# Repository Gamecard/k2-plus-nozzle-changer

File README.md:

# K2 Plus Nozzle Changer – Düsenwechsler für den Creality K2 Plus

**English summary:** This repository contains a tool changer concept for the Creality K2 Plus 3D printer. Every colour gets its
own cartridge with its own hotend and its own filament path; the print head parks one cartridge in a passive dock at the front
and picks up another, so filament never has to be unloaded, cut or purged. Included are the mechanical design description
(prototype 19 v2), a complete, generator-built KiCad design of a new toolhead board (P19, revision 10) and a carrier
board for a Raspberry Pi Compute Module 5 as the printer's Klipper host (alpha 2), each with Gerber, BOM and
pick-and-place files. Status: designed and checked by calculation and simulation; not yet built or tested on a
printer. Not affiliated with Creality. Licences: hardware design CERN-OHL-W v2 (`LICENSE`), program code
GPL-3.0-or-later (`LICENSE-GPL-3.0.txt`).

Stand: konstruiert und rechnerisch geprüft, noch nicht gebaut und nicht am Drucker erprobt. Lizenz und Haftung:
[`LIZENZ-UND-HAFTUNG.md`](LIZENZ-UND-HAFTUNG.md).

## Worum es geht

Der Creality K2 Plus druckt mehrfarbig, indem er das Filament im Druckkopf wechselt: altes Filament zurückziehen, abschneiden,
neues laden und die Düse durchspülen. Das kostet Zeit und Material.

Dieses Projekt geht einen anderen Weg, ähnlich wie ein Werkzeugwechsler („Toolchanger“):

- Jede Farbe bekommt eine eigene **Patrone**. Eine Patrone ist ein gefrästes Aluminiumteil, in dem ein komplettes **Hotend**
  sitzt (Düse, Heizblock, Heatbreak – also der heiße Teil, der das Filament schmilzt) und durch das das Filament dieser Farbe läuft.
- Am Druckkopf sitzt immer genau eine Patrone. Die übrigen liegen in einer **Ablage** (Parkplätze) vorne über der Tür.
- Beim Farbwechsel legt der Kopf seine Patrone in der Ablage ab und nimmt eine andere auf. Das Filament bleibt dabei in seiner
  Patrone geladen – kein Entladen, kein Schneiden, kein Spülen.
- Der Antrieb des Filaments (Förderräder und Motor) bleibt fest im Kopf; die Förderräder greifen das Filament durch ein Fenster
  der jeweils angedockten Patrone.

Wichtigste Vorgabe der Konstruktion: Der Drucker soll **keine Druckfläche verlieren**. Die Düse liegt deshalb an derselben Stelle
wie beim Original-Kopf, der Kopf ist nicht breiter als das Original (55 mm), und die Ablage passt in den Spalt zwischen Kopf und
Tür.

## Wie ein Wechsel abläuft (Grundprinzip)

1. Der Kopf fährt vor den Platz der Ablage, auf dem er seine Patrone ablegen will.
2. Er fährt langsam nach vorn in den Platz. Die Patrone gleitet mit zwei Leisten auf ihrer Oberseite in Schienen der Ablage und
   rastet dort mit federnden Kugeln ein.
3. Zwei kleine **Hubmagnete** im Kopf öffnen kurz einen federbelasteten Riegel; die Patrone ist jetzt nur noch in der Ablage gehalten.
4. Der Kopf fährt zurück, fährt seitlich zur gewünschten anderen Patrone und mit offenem Riegel in deren Platz.
5. Die Hubmagnete werden stromlos, die Feder schließt den Riegel, ein **Hall-Sensor** meldet „Riegel zu“.
6. Der Kopf fährt zurück und zieht die Patrone dabei aus der Rastung. Die Patrone ist in jedem Moment entweder am Kopf verriegelt
   oder in der Ablage eingerastet.

Die nächste Patrone soll schon in der Ablage vorgeheizt werden. Gerechnet ergibt sich eine Wechselzeit von etwa 1,4 bis 1,6 Sekunden
(ohne Vorheizen und ohne die Fahrt vom Druckteil zur Ablage). Einzelheiten stehen in [`prototyp-19v2/README.md`](prototyp-19v2/README.md).

## Inhalt des Repositorys

| Ordner / Datei | Inhalt |
|---|---|
| [`prototyp-19v2/`](prototyp-19v2/) | Beschreibung der Mechanik (Prototyp 19 v2): Aufbau, Wechselablauf, Baugruppen, Kaufteile, offene Punkte; Bilder |
| [`prototyp-19v2/cad/`](prototyp-19v2/cad/) | CAD-Daten: SolidCraft-Modell, STEP der Baugruppe, STL der Druckteile (ohne fremde Bezugsmodelle, siehe dort) |
| [`cm5-carrier-pcb/`](cm5-carrier-pcb/) | Trägerplatine „K2-CM5-Träger Alpha 2“ für ein Raspberry Pi Compute Module 5 als Steuerrechner des Druckers: KiCad-Projekt, Python-Generator, Fertigungsdaten für JLCPCB, Lastenheft, Aufbau- und Bestellunterlagen |
| [`toolhead-pcb/`](toolhead-pcb/) | Eigene Kopfplatine „P19, Fassung 10“: KiCad-Projekt, Python-Generator, Fertigungsdaten für JLCPCB, Schaltungsbeschreibung, Kabelliste, Prüfberichte, Klipper-Beispielkonfiguration |
| [`LICENSE`](LICENSE) | Lizenztext CERN-OHL-W v2 (Hardware-Entwurf) |
| [`LICENSE-GPL-3.0.txt`](LICENSE-GPL-3.0.txt) | Lizenztext GNU GPL Version 3 (Programmcode) |
| [`LIZENZ-UND-HAFTUNG.md`](LIZENZ-UND-HAFTUNG.md) | Lizenzhinweis, Kurzfassung, Ausnahmen, Haftungsausschluss |

## Die Kopfplatine in einem Satz

Die Platine ersetzt die Original-Kopfplatine des K2 Plus. Sie wird mit 24–48 V versorgt, spricht mit dem Steuerrechner über
**CAN-Bus** (eine Zweidraht-Datenleitung, wie sie viele Klipper-Druckköpfe nutzen) und zusätzlich über **USB** (für Kamera und
Cartographer-Sensor über einen eingebauten USB-Hub) und trägt Motortreiber, Schaltausgänge und alle Sensoreingänge, die der
Wechsler braucht. Einzelheiten: [`toolhead-pcb/README.md`](toolhead-pcb/README.md).

**Wichtig:** Die Platine hat keinen Anschluss mehr für das Original-Kopfkabel des Druckers. Für den Betrieb ist ein **eigenes
Kabel vom Drucker zum Kopf** nötig (Versorgung + CAN und USB).

## Der Steuerrechner in einem Satz

Die Kopfplatine braucht einen Steuerrechner mit Klipper, der CAN und USB bereitstellt. Dafür liegt hier die Trägerplatine für
ein **Raspberry Pi Compute Module 5** bei: Sie ersetzt die Original-Steuerplatine des K2 Plus, wird mit 24 V versorgt, spricht
über RS485 und CAN mit dem Drucker und hat Anschlüsse für Display (DSI mit vier Datenleitungen, HDMI als Nachrüstoption,
USB für Touch), Lüfter und eine serielle Konsole. Die Vorgängerfassung Alpha 1 ist gebaut und läuft im Drucker; Alpha 2 ist
fertig entworfen und geprüft, aber noch nicht gefertigt. Einzelheiten: [`cm5-carrier-pcb/README.md`](cm5-carrier-pcb/README.md).

## Stand und bekannte offene Punkte (Stand 22.11.2026)

**Was geprüft ist** (nur rechnerisch bzw. in Simulation und im CAD):

- Mechanik: Platzbedarf gegen die Druckfläche, Kollisionsfreiheit des ganzen Wechselablaufs, Montierbarkeit jeder Schraube,
  Festigkeit und Steifigkeit (FEM), Eigenfrequenzen, Wärme an Kopf und Patrone, Toleranzen, Wechselzeit.
- Kopfplatine: elektrische Regelprüfung des Schaltplans (ERC) und der Platine (DRC) ohne Fehler, keine offenen Verbindungen,
  Netzliste gegen eine unabhängige Soll-Tabelle geprüft, kritische Leitungen (Längen, Breiten, USB-Paare) geprüft, Fertigungsnutzen
  geprüft. Steckbarkeit aller Stecker und Kabelwege im CAD-Modell des Kopfs geprüft.

**Was nicht geprüft ist:**

- Nichts ist gebaut. Keine Patrone, keine Ablage, keine Platine wurde gefertigt oder in Betrieb genommen.
- Viele Kaufteil-Maße und -Kennwerte sind Annahmen oder aus Datenblättern übernommen, nicht am Teil gemessen.
- Die Firmware-Seite (Klipper-Konfiguration, Makros für den Wechsel) liegt nur als Entwurf vor und ist nirgends eingespielt.

**Offene Punkte (Auswahl):**

- Andockkraft: Der Kopf drückt beim Andocken mit etwa 50–64 N gegen die Ablage. Ob der Y-Antrieb des Druckers das sicher
  schafft, ist nur abgeschätzt und muss am Drucker bestätigt werden.
- Zum Andocken fährt der Kopf 18,5 mm weiter nach vorn als beim Drucken. Ob die Fahrgrenze in der Klipper-Konfiguration dafür
  reicht oder angepasst werden muss, ist offen.
- Führung der Patronenkabel und Filamentschläuche vom Kopf zur Filamentzufuhr (CFS) ist noch nicht ausgelegt.
- Heizungen und Temperaturfühler der Patronen hängen an einer eigenen **Heizplatine**, die noch nicht Teil dieses Repositorys ist
  (Konzeptstand).
- Kopfplatine: Lagerbestand des 2-poligen JST-GH-Steckers beim Bestücker am Bestelltag prüfen; Pin 1 und Drehung der gepolten
  Teile in der Bestellvorschau ansehen; das neue Kabel Drucker → Kopf ist zu konfektionieren.
- Einige Kabelabgänge an Geräten (Bauteillüfter, LED-Kette, Probe) sind angenommen, nicht gemessen.

## Lizenz und Haftung

Der Hardware-Entwurf steht unter der **CERN Open Hardware Licence Version 2 – Weakly Reciprocal (CERN-OHL-W v2)**, der
Programmcode (Generator, Werkzeuge, Bauskript, Klipper-Beispiel) unter der **GNU General Public License Version 3 oder
später**. Die vollständigen Lizenztexte enthalten [`LICENSE`](LICENSE) und [`LICENSE-GPL-3.0.txt`](LICENSE-GPL-3.0.txt); Kurzfassung, Ausnahmen (KiCad-Bibliotheken, Herstellerdaten, fremde Modelle) und den
Haftungsausschluss enthält [`LIZENZ-UND-HAFTUNG.md`](LIZENZ-UND-HAFTUNG.md). Hinweis: Die Platinen arbeiten mit
bis zu 48 V, Motor- und Heizlasten.

## Hinweis zu Marken

Dieses Projekt ist **kein Produkt von Creality** und steht in keiner Verbindung zu Creality oder anderen genannten Herstellern.
Marken- und Produktnamen (z. B. Creality, K2 Plus, CFS, Bambu Lab, Micro Swiss, Cartographer, JST, JLCPCB) dienen nur der
Bezeichnung der Teile und Geräte, mit denen der Entwurf zusammenarbeiten soll.

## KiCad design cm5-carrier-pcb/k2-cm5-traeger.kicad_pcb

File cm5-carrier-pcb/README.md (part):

# K2-CM5-Träger Alpha 2 – Layout-Entwurf (22.11.2026)

**English summary:** Carrier board for a Raspberry Pi Compute Module 5 that replaces the original controller board of the
Creality K2 Plus (Klipper host): 24 V input, RS485 and CAN to the printer, the printer's original 50-pin flat cable, DSI
display connector with 4 lanes, optional HDMI (connector not populated), USB-A for touch, switched 5 V for displays, fan and
debug console connectors. The KiCad files are produced by a Python generator. Status: design complete and checked
(ERC/DRC clean), not yet manufactured or tested. Predecessor Alpha 1 was built and runs in the printer.

Stand: Entwurf fertig und geprüft, noch nicht gefertigt und nicht erprobt. Lizenz: Hardware-Unterlagen **CERN-OHL-W v2**,
Programmcode (Generator, Werkzeuge) **GPL-3.0-or-later**; Lizenz und Haftung: [`../LIZENZ-UND-HAFTUNG.md`](../LIZENZ-UND-HAFTUNG.md).
Quelle: `github.com/Gamecard/k2-plus-nozzle-changer`.

> **Status (22.11.2026): Alpha 2 – Entwurf, nicht bestellt, nicht gefertigt.** Grundlage ist Alpha 1 (gefertigt, seit
> 09.11.2026 im Drucker). Unverändert: Breite, Lochbild, CM5-Lage, Flachkabel J1, 24-V-Eingang J7, CAN J9b, RS485 J11,
> Notfall-USB J10. Neu bzw. geändert: Display-Stecker J12 (richtig belegt, 4 Lanes), freie Displaywahl mit HDMI
> (Buchse J16 als Nachrüstoption, nicht bestückt), USB-A J17 für Touch über einen Hub, Display-5 V J13 bis 2,6 A,
> Lüfter J14, Konsole J15, CAN-Abschluss als Lötbrücke, Kante B um 16,5 mm verlängert, eigener Nutzen für die
> Fertigung. Begründungen: [`ALPHA2-LASTENHEFT.md`](ALPHA2-LASTENHEFT.md). Prüfstand: [Prüfungen](#prüfungen).

> **Unterlagen:** [`ALPHA2-LASTENHEFT.md`](ALPHA2-LASTENHEFT.md) · [`BESTELLUNG-JLC.md`](BESTELLUNG-JLC.md) ·
> [`KOMPROMISSE-UND-OFFENE-PUNKTE.md`](KOMPROMISSE-UND-OFFENE-PUNKTE.md) · Inbetriebnahme (Alpha 1, mit Abweichungen):
> [`AUFBAU-UND-INBETRIEBNAHME.md`](AUFBAU-UND-INBETRIEBNAHME.md) · Konzept: [`KONZEPT.md`](KONZEPT.md) ·
> Bestückungsübersicht: `ausgabe/bestueckung_oben.png`, `ausgabe/bestueckung_unten.png`

## Zweck

Der Träger ersetzt das T113-Upper-Board des K2 Plus. Er trägt ein **Raspberry Pi Compute Module 5 (CM5)** direkt (zwei
100-pol. Steckverbinder, 1,5 mm Bauhöhe), versorgt es aus den 24 V des Druckers und verbindet es über das
Original-Flachkabel (J1) mit dem Drucker. Er sitzt hinter dem Display im Displaygehäuse (Dome L1–L4), Bauteilseite
zum Display.

## Unterschiede zu Alpha 1

| Punkt | Alpha 1 | Alpha 2 | Stecker / CM5-Pins |
|---|---|---|---|
| Umriss | 90,0 × 56,1 mm | **90,0 × 72,6 mm** (Kante B 16,5 mm länger, alle Alpha-1-Lagen gleich) | – |
| Display-Stecker | Hirose FH12 (Kontakte unten), Belegung **gespiegelt** | Buchse mit **Kontakten oben**, Pad n = Kabelleiter n, jeder Kontakt gegen das CM5-IO-Board geprüft; Kabel **mit Kontakten nach oben** stecken | J12 |
| DSI-Lanes | D0, D1 + Takt | **D0–D3 + Takt**, 100 Ω, ohne Via, gleich lang | J12; CM5 175–189, **193/195 (D2), 194/196 (D3)** |
| HDMI | – | **J16** HDMI Typ A, alle 4 TMDS-Paare 100 Ω ohne Via, DDC/CEC/HPD mit ESD, 5 V begrenzt – **Buchse nicht bestückt** | HDMI1: 143–166 |
| USB-Host (Touch) | – | **J17** USB-A über Hub U19 (CH334R) am Hub-Port, 5 V 0,89–1,06 A, schaltbar | USB3-1 (163/165), VBUS_EN (Pin 111) |
| 5 V für Displays | – | **J13** JST GH 6-pol., Lastschalter **2,33–2,63 A**, an nach Reset, abschaltbar | GPIO26 (Pin 24) EN, GPIO6 (Pin 30) Fehler |
| Lüfter | – | **J14** JST SH 4-pol. wie Raspberry Pi 5, 5 V geschaltet (0,49–0,60 A) | Pin 16 Fan_Tacho, Pin 19 Fan_PWM, Pin 111 VBUS_EN |
| Konsole | – | **J15** JST SH 3-pol. nach Pi-Debugstecker-Spezifikation | GPIO8/9 (Pin 39/40) = UART3 |
| CAN-Controller | SPI0 (GPIO8–11) | **SPI1** (GPIO18–21), INT GPIO25 unverändert | Pins 49/26/27/25 statt 39/40/44/38 |
| CAN-Abschluss | Stiftleiste + Kappe (Kappe fehlte ab Werk) | **Lötbrücke, ab Werk geschlossen** | JP_CAN_TERM |
| RS485-Abschluss | Stiftleiste | **Lötbrücke, ab Werk offen** | JP_485_TERM |
| Fertigung | Einzelplatine, JLC setzte Ränder mit V-Cut | **eigener Nutzen** mit Frässchlitz und Mausbiss-Stegen | – |
| Bauergebnis | jede Generierung anders | zweimal gebaut = byte-gleich | – |

Weggelassen wurde **keine** Funktion von Alpha 1. Die Hub-Leitung am Flachkabel J1 läuft jetzt über den Hub U19
(Port 1); das Gerät am Flachkabel sieht weiterhin einen USB-2.0-Anschluss.

## Welche Displays gehen

| Display | Anschluss | Versorgung | Grenzen |
|---|---|---|---|
| DSI 22-pol. (Raspberry Pi 5 / CM5-IO-Belegung, 1–4 Lanes), z. B. Raspberry Pi Touch Display 2, Waveshare DSI | J12, Kabel mit Kontakten nach oben | 3,3 V aus J12 (eigener Wandler, 2 A); 5 V bei Bedarf aus J13 | nur DSI1 (ein Display); Touch über I2C an J12 |
| DSI 15-pol. (Raspberry-Pi-4-Belegung, 2 Lanes) | J12 über Adapterkabel 22 → 15 (Raspberry-Pi-5-Displaykabel) | wie oben | nur 2 Lanes (D2/D3 sind am 15-pol. Kabel nicht vorhanden) |
| HDMI mit USB-Touch | J16 (Buchse **nachlöten**, Anleitung unten) + J17 USB-A | 5 V aus J13 (bis 2,33 A sicher, siehe Budget) oder über das USB-Kabel aus J17 (≤ 0,89 A) | HDMI1 bis 4K60 laut CM5-Datenblatt; ohne nachgelötete Buchse kein HDMI |
| HDMI ohne Touch | J16 (nachlöten) | J13 | wie oben |
| Displays mit eigenem 5-V-Eingang (Stiftleiste, Micro-USB, USB-C) | J12 oder J16 | **J13**, Kabel GH 6-pol. → Displaystecker | ≥ 2 A nur, wenn CM5 + USB-A + Lüfter zusammen unter ≈ 3 A bleiben (normal ≈ 1,4 A) |

## Stecker

Draufsicht von oben, Kante A links (Flachkabel), B oben (HDMI/USB-A), C rechts (Display), D unten.

| Stecker | Funktion | Bauform | Belegung | Lage |
|---|---|---|---|---|
| J1 | Original-Flachkabel zum Drucker | FPC 50-pol. 0,5 mm (XUNPU FPC-05FB-50PH20) | wie Alpha 1 (Pin n = Breakout n) | Kante A |
| J7 | 24-V-Eingang | XT30 liegend | 2 = +24 V, 1 = GND | Kante A oben |
| J9b | CAN (Toolhead/Mainboard-Ersatz) | JST GH 3-pol. stehend | 1 CANH, 2 CANL, 3 GND | innen, rechts von L1 (Drossel) |
| J10 | Notfall-USB-C (rpiboot, 5-V-Notversorgung) | USB-C stehend | USB 2.0 OTG | innen, links |
| J11 | RS485-Abgriff | JST GH 3-pol. stehend | 1 A, 2 B, 3 GND | Kante D |
| **J12** | **DSI-Display** (MIPI1 = DSI1) | FPC 22-pol. 0,5 mm, **Kontakte oben**, Schieber | Raspberry Pi 5 / CM5-IO (Tabelle unten) | Kante C, Mitte |
| **J13** | **5 V für Displays** | JST GH 6-pol. stehend | 1–3 = 5 V, 4–6 = GND | Kante B rechts |
| **J14** | **Lüfter** | JST SH 4-pol. stehend | 1 = 5 V, 2 = PWM, 3 = GND, 4 = Tacho (wie Pi 5) | rechts oben neben dem CM5 |
| **J15** | **Serielle Konsole** | JST SH 3-pol. stehend | 1 = RX (in den CM5), 2 = GND, 3 = TX (aus dem CM5) | Kante C unten, unter J12 |
| **J16** | **HDMI** (HDMI1) – **nicht bestückt** | HDMI Typ A liegend (Amphenol 10029449-001RLF) | HDMI-Norm | Kante B Mitte |
| **J17** | **USB-A Host** (Touch, USB 2.0) | USB-A liegend (Molex 67643-2911) | USB-Norm | Kante B links |

## Lötbrücken und Steckbrücke

*Lötbrücke:* zwei oder drei Kupferflächen nebeneinander. „Geschlossen“ heißt: ab Werk durch einen schmalen Kupfersteg
verbunden – zum Ausschalten den Steg mit einem Cutter durchtrennen, zum Wiedereinschalten Lötzinn darüber. „Offen“
heißt: ab Werk getrennt – zum Einschalten mit einem Zinntropfen verbinden.

| Bezeichnung | Seite | Funktion | ab Werk |
|---|---|---|---|
| JP_CAN_TERM | oben | CAN-Abschluss 120 Ω (Träger = Busende) | **geschlossen** |
| JP_485_TERM | oben | RS485-Abschluss 120 Ω | **offen** (Bus wird heute vom K2-Mainboard abgeschlossen) |
| JP2 / JP3 | unten | RS485-Ruhevorspannung A/B | geschlossen |
| JP5 | unten | 5-V-Notversorgung über USB-C in den Power-Mux | geschlossen |
| JP6 / JP7 | unten | CC1/CC2 der USB-C-Buchse an den CM5 (R43/R44 nur, wenn offen) | geschlossen |
| JP_FAN_EN (3-pol.) | unten | Freigabe Lüfter-5 V: 1–2 = VBUS_EN (aus, wenn der CM5 heruntergefahren ist), 2–3 = CM5-3,3 V | **1–2 geschlossen** |
| JP_BOOT | oben | Stiftleiste: Steckbrücke gesteckt = rpiboot über J10 | offen (keine Kappe) |

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
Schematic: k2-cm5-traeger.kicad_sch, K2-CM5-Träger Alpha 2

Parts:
C1, C2: 22p; C_0805_2012Metric; MPN CL21C220JBANNNC; LCSC C1804
C3, C5, C6, C7, C11, C12, C22, C25, C27, C30, C31, C32, C33, C39, C40, C42, C43, C46, C47: 100n; C_0805_2012Metric; MPN CC0805KRX7R9BB104; LCSC C49678
C4, C18, C34, C37, C41, C44, C45: 10u; C_0805_2012Metric; MPN CL21A106KAYNNNE; LCSC C15850
C8: 22n; C_0805_2012Metric; MPN CC0805KRX7R9BB223; LCSC C107147
C9, C10: 10u50; C_1206_3216Metric; MPN CL31A106KBHNNNE; LCSC C13585
C13: 33p; C_0805_2012Metric; MPN CC0805JRNPO9BN330; LCSC C107115
C14, C15, C16, C17, C19, C20, C21: 22u25; C_1206_3216Metric; MPN CL31A226KAHNNNE; LCSC C12891
C28: 1n2kV; C_1206_3216Metric; MPN 1206B102K202NT; LCSC C9196
C35, C36, C38, C48, C49: 22u6; C_0805_2012Metric; MPN CL21A226MQQNNNE; LCSC C5674
D1, D2, D3, D20: USBLC6-2SC6; SOT-23-6; MPN USBLC6-2SC6; LCSC C7519
D4, D19: SRV05-4; SOT-23-6; MPN SRV05-4; LCSC C5240367
D5: SM712; SOT-23; MPN SM712; LCSC C502564
D6: NUP2105L; SOT-23; MPN NUP2105LT1G; LCSC C14486
D7: TPD4E05U06; USON-10_2.5x1.0mm_P0.5mm; MPN TPD4E05U06DQAR; LCSC C138714
D8: SMFJ28A; D_SOD-123F; MPN SMFJ28A; LCSC C5439963
D10: LED 0805 rot; LED_0805_2012Metric; MPN NCD0805R1; LCSC C84256
D11, D12, D13: LED 0805 grün; LED_0805_2012Metric; MPN KT-0805G; LCSC C2297
D14: LED 0805 gelb; LED_0805_2012Metric; MPN KT-0805Y; LCSC C2296
D15, D16: SMF5.0A; D_SOD-123F; MPN SMF5.0A; LCSC C193402
F1: 3A tauschbar; Sicherungshalter_Littelfuse_157_Nano2_2410; MPN 0157003.DR; LCSC C187520
F3: PTC 0,5A 30V; Fuse_1812_4532Metric; MPN SMD1812P050TF/30; LCSC C12559
FID1, FID2, FID3, FID4, FID5, FID6: Passermarke; Fiducial_1mm_Mask2mm
H1, H2, H3, H4: Befestigung T113-Platz (M3); Bohrung_3.5mm_T113_Kopf5.5mm
J1: FPC-05FB-50PH20; FFC_XUNPU_FPC-05FB-50PH20_1x50_P0.5mm_Horizontal; MPN FPC-05FB-50PH20; LCSC C2856838
J2: CM5 (2x DF40C-100DS-0.4V(51)); CM5_Modul_2xDF40C-100DS-0.4V51_1.5mm; MPN DF40C-100DS-0.4V(51); LCSC C597931
J7: XT30 24V; AMASS_XT30PW-M_1x02_P2.50mm_Horizontal; MPN XT30PW-M30.G.Y; LCSC C431092
J9b: CAN H/L/GND; JST_GH_BM03B-GHS-TBT_1x03-1MP_P1.25mm_Vertical; MPN BM03B-GHS-TBT(LF)(SN); LCSC C161691
J10: USB-C stehend; USB_C_Buchse_stehend_16P_TYPE-C-16P-LTH6.8; MPN TYPE-C 16P LTH6.8; LCSC C5187468
J11: RS485 A/B/GND; JST_GH_BM03B-GHS-TBT_1x03-1MP_P1.25mm_Vertical; MPN BM03B-GHS-TBT(LF)(SN); LCSC C161691
J12: DSI 22-pol. Kontakte oben; FPC_0.5K-AS-22PWB_1x22_P0.5mm_Kontakte_oben_Horizontal; MPN 0.5K-AS-22PWB-RW; LCSC C53120858
J13: 5V Display; JST_GH_BM06B-GHS-TBT_1x06-1MP_P1.25mm_Vertical; MPN BM06B-GHS-TBT(LF)(SN); LCSC C189892
J14: Lüfter; JST_SH_BM04B-SRSS-TB_1x04-1MP_P1.00mm_Vertical; MPN BM04B-SRSS-TBT(LF)(SN); LCSC C495539
J15: Konsole UART; JST_SH_BM03B-SRSS-TB_1x03-1MP_P1.00mm_Vertical; MPN BM03B-SRSS-TBT(LF)(SN); LCSC C495538
J16: HDMI A (n. b.); HDMI_A_Amphenol_10029449-x01xLF_Horizontal; MPN 10029449-001RLF; LCSC C428493; not fitted
J17: USB-A Host; USB_A_Molex_67643_Horizontal; MPN 67643-2911; LCSC C293351
JP2: Bias A; SolderJumper-2_P1.3mm_Bridged_RoundedPad1.0x1.5mm
JP3: Bias B; SolderJumper-2_P1.3mm_Bridged_RoundedPad1.0x1.5mm
JP5: VBUS; SolderJumper-2_P1.3mm_Bridged_RoundedPad1.0x1.5mm
JP6: CC1; SolderJumper-2_P1.3mm_Bridged_RoundedPad1.0x1.5mm
JP7: CC2; SolderJumper-2_P1.3mm_Bridged_RoundedPad1.0x1.5mm
JP_485_TERM: 485 120R; SolderJumper-2_P1.3mm_Open_RoundedPad1.0x1.5mm
JP_BOOT: RPIBOOT; Stiftleiste_1x2_P2.54mm_SMD_stehend; MPN HX PZ2.54-1x2P TP-YQ; LCSC C41417359
JP_CAN_TERM: CAN 120R; SolderJumper-2_P1.3mm_Bridged_RoundedPad1.0x1.5mm
JP_FAN_EN: 1-2 zu; SolderJumper-3_P1.3mm_Bridged12_RoundedPad1.0x1.5mm
L1: 4,7µH; L_Changjiang_FXL0630; MPN FXL0630-4R7-M; LCSC C167220
L2: 2,2µH; L_1008_2520Metric; MPN WPN252010H2R2MT; LCSC C97031
R1, R2, R3, R4, R15, R16, R20, R28, R41, R42: 1k; R_0805_2012Metric; MPN 0805W8F1001T5E; LCSC C17513
R9, R10, R45, R54, R58: 100k; R_0805_2012Metric; MPN 0805W8F1003T5E; LCSC C149504
R11, R12, R13, R14, R18, R30, R50, R52, R53, R55: 10k; R_0805_2012Metric; MPN 0805W8F1002T5E; LCSC C17414
R17, R19, R56, R57: 120; R_0805_2012Metric; MPN 0805W8F1200T5E; LCSC C17437
R23: 5m; R_2512_6332Metric; MPN RLM25FEER005; LCSC C185817
R24: 10m; R_2512_6332Metric; MPN HoLLR2512-2W-10mR-1%; LCSC C2962784
R26: 105k; R_0805_2012Metric; MPN 0805W8F1053T5E; LCSC C17410
R27: 19k1; R_0805_2012Metric; MPN 0805W8F1912T5E; LCSC C17508
R29: 33k; R_0805_2012Metric; MPN 0805W8F3302T5E; LCSC C17633
R31: 18k7; R_0805_2012Metric; MPN 0805W8F1872T5E; LCSC C17499
R36, R37: 75; R_0805_2012Metric; MPN 0805W8F750JT5E; LCSC C17820
R38, R48, R49: 2k2; R_0805_2012Metric; MPN 0805W8F2201T5E; LCSC C17520
R39, R40: 470; R_0805_2012Metric; MPN 0805W8F4700T5E; LCSC C17710
R43, R44: 5k1; R_0805_2012Metric; MPN 0805W8F5101T5E; LCSC C27834; not fitted
R46, R51: 22k; R_0805_2012Metric; MPN 0805W8F2202T5E; LCSC C17560
R59: 150k; R_0805_2012Metric; MPN 0805W8F1503T5E; LCSC C17470
R60: 56k; R_0805_2012Metric; MPN 0805W8F5602T5E; LCSC C17756
T1: H1102NLT; Uebertrager_SMD_H1102NLT_12.7x7.1mm; MPN H1102NLT; LCSC C18584
TP1, TP2: GND; TestPoint_Pad_D1.5mm
TP3: 5V; TestPoint_Pad_D1.5mm
TP4: 3V3; TestPoint_Pad_D1.5mm
TP5: RUN; TestPoint_Pad_D1.5mm
TP6: BOOT; TestPoint_Pad_D1.5mm
TP7: PWR; TestPoint_Pad_D1.5mm
TP10: 24V; TestPoint_Pad_D1.5mm
TP11: BR5V; TestPoint_Pad_D1.5mm
TP12: PWR_FAIL; TestPoint_Pad_D1.5mm
U1: MCP2518FD; SOIC-14_3.9x8.7mm_P1.27mm; MPN MCP2518FDT-H/SL; LCSC C626759
U2: SN65HVD230; SOIC-8_3.9x4.9mm_P1.27mm; MPN SN65HVD230DR; LCSC C12084
U3: THVD1450DR; SOIC-8_3.9x4.9mm_P1.27mm; MPN THVD1450DR; LCSC C2671361
U4, U5: INA226; MSOP-10_3x3mm_P0.5mm; MPN INA226AIDGSR; LCSC C49851
U7: LMR51450SDRRR; WSON-12-1EP_3x3mm_P0.5mm_EP1.5x2.5mm; MPN LMR51450SDRRR; LCSC C6890985
U8: TPS2121RUXR; Texas_RUX_VQFN-HR-12_2x2.5mm_P0.5mm; MPN TPS2121RUXR; LCSC C485916
U10, U11, U12, U13, U17: SN74LVC1G125; SOT-23-5; MPN SN74LVC1G125DBVR; LCSC C23654
U14: TLV62569DBVR; SOT-23-5; MPN TLV62569DBVR; LCSC C141836
U15, U16, U18, U20: TPS25221DBVR; SOT-23-6; MPN TPS25221DBVR; LCSC C470965
U19: CH334R; QSOP-16_3.9x4.9mm_P0.635mm; MPN CH334R; LCSC C4154405
Y1: 40 MHz; Crystal_SMD_3225-4Pin_3.2x2.5mm; MPN S3240000151040; LCSC C426990
Y2: 12 MHz; Crystal_SMD_3225-4Pin_3.2x2.5mm; MPN X322512MSB4SI; LCSC C9002

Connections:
B26_UART2_TX: D4.1 (IO1), J1.26, R1.1
B28_UART2_RX: D4.3 (IO2), J1.28, R2.1
B30_UART4_TX: D4.4 (IO3), J1.30, R3.1
B32_UART4_RX: D4.6 (IO4), J1.32, R4.1
BR_5V: J1.45, J1.46, J1.47, J1.48, J1.49, J1.50, R15.1, R38.1, TP11.1
CAM_DM: D1.3 (I/O2), D1.4 (I/O2), J1.37, J2.136 (USB3-0-DM)
CAM_DP: D1.1 (I/O1), D1.6 (I/O1), J1.38, J2.134 (USB3-0-DP)
CAM_GPIO0: J2.97 (CAM_GPIO0), J12.17
CAM_GPIO1: J2.100 (CAM_GPIO1), J12.18
CANH: D6.1 (K), J9b.1, R19.1, U2.7 (CANH)
CANL: D6.2 (K), J9b.2, JP_CAN_TERM.2 (B), U2.6 (CANL)
CAN_CS: J2.49 (GPIO18), U1.13 (~CS)
CAN_INT: J2.41 (GPIO25), R18.2, U1.4 (~INT)
CAN_MISO: J2.26 (GPIO19), U1.12 (SDO)
CAN_MOSI: J2.27 (GPIO20), U1.11 (SDI)
CAN_OSC1: C1.1, U1.6 (OSC1), Y1.1
CAN_OSC2: C2.1, U1.5 (OSC2), Y1.3
CAN_RX: U1.2 (RXCAN), U2.4 (R)
CAN_SCK: J2.25 (GPIO21), U1.10 (SCK)
CAN_TERM: JP_CAN_TERM.1 (A), R19.2
CAN_TX: U1.1 (TXCAN), U2.1 (D)
CC1_CM5: J2.94 (CC1), JP6.2 (B)
CC2_CM5: J2.96 (CC2), JP7.2 (B)
CM5_3V3: C3.1, C4.1, C5.1, C6.1, C7.1, C25.1, C30.1, C31.1, C32.1, C33.1, C42.1, C45.1, C46.1, J2.78 (GPIO_VREF), J2.84 (CM5_3.3V), J2.86 (CM5_3.3V), JP_FAN_EN.3 (B), R11.1, R12.1, R14.1, R18.1, R39.1, R40.1, R41.1, R42.1, R48.1, R49.1, R50.1, R52.1, R53.1, R55.1, R58.1, TP4.1, U1.14 (VDD), U2.3 (VCC), U3.8 (VCC), U4.6 (VS), U5.2 (A0), U5.6 (VS), U10.5 (VCC), U11.5 (VCC), U12.5 (VCC), U13.5 (VCC), U14.1 (EN), U17.5 (VCC), U18.3 (EN), U19.12 (V5), U19.13 (VDD33)
CM5_5V: C19.1, C20.1, C21.1, C22.1, C34.1, J2.77 (5V), J2.79 (5V), J2.81 (5V), J2.83 (5V), J2.85 (5V), J2.87 (5V), R24.2, TP3.1, U5.8 (Vbus), U5.9 (Vin-), U14.4 (VIN)
CON_RX_EXT: J15.1, R57.1
CON_RX_PUF: R57.2, R58.2, U17.2
CON_TX_EXT: J15.3, R56.2
DISP5V_EN: J2.24 (GPIO26), R52.2, U15.3 (EN)
DISP_5V: C38.1, C39.1, D16.1 (A1), J13.1, J13.2, J13.3, U15.6 (OUT)
DISP_ILIM: R51.1, U15.5 (ILIM)
DSI1_C_N: J2.187 (MIPI1_C_N), J12.8
DSI1_C_P: J2.189 (MIPI1_C_P), J12.9
DSI1_D0_N: J2.175 (MIPI1_D0_N), J12.2
DSI1_D0_P: J2.177 (MIPI1_D0_P), J12.3
DSI1_D1_N: J2.181 (MIPI1_D1_N), J12.5
DSI1_D1_P: J2.183 (MIPI1_D1_P), J12.6
DSI1_D2_N: J2.193 (MIPI1_D2_N), J12.11
DSI1_D2_P: J2.195 (MIPI1_D2_P), J12.12
DSI1_D3_N: J2.194 (MIPI1_D3_N), J12.14
DSI1_D3_P: J2.196 (MIPI1_D3_P), J12.15
DSI_3V3: C35.1, C36.1, J12.22, L2.2, R45.1
DSI_FB: R45.2, R46.1, U14.5 (FB)
DSI_SCL: J2.35 (ID_SC), J12.20, R48.2
DSI_SDA: J2.36 (ID_SD), J12.21, R49.2
DSI_SW: L2.1, U14.3 (SW)
ETH0_N: D7.5 (D2-), D7.6 (NC), J2.10 (Ethernet_Pair0_N), T1.6 (RD+)
ETH0_P: D7.4 (D2+), D7.7 (NC), J2.12 (Ethernet_Pair0_P), T1.8 (RD-)
ETH1_N: D7.2 (D1-), D7.9 (NC), J2.6 (Ethernet_Pair1_N), T1.3 (TD-)
ETH1_P: D7.1 (D1+), D7.10 (NC), J2.4 (Ethernet_Pair1_P), T1.1 (TD+)
ETH_A_N: J1.2, T1.14 (TX-)
ETH_A_P: J1.1, T1.16 (TX+)
ETH_BOB: C28.1, R36.2, R37.2
ETH_B_N: J1.5, T1.9 (RX-)
ETH_B_P: J1.4, T1.11 (RX+)
ETH_CT_A: R36.1, T1.15 (C_TX)
ETH_CT_B: R37.1, T1.10 (C_RX)
ETH_CT_PHY: C27.1, T1.2 (C_TD), T1.7 (C_RD)
ETH_NLED2: D14.1 (K), J2.17 (Ethernet_nLED2)
ETH_NLED3: D13.1 (K), J2.15 (Ethernet_nLED3)
FAN_5V: C41.1, J14.1, U16.6 (OUT)
FAN_EN: JP_FAN_EN.2 (C), U16.3 (EN)
FAN_ILIM: R54.1, U16.5 (ILIM)
FAN_PWM: J2.19 (Fan_PWM), J14.2, R55.2
FAN_TACHO: J2.16 (Fan_Tacho), J14.4
GND: C1.2, C2.2, C3.2, C4.2, C5.2, C6.2, C7.2, C8.2, C9.2, C10.2, C11.2, C14.2, C15.2, C16.2, C17.2, C18.2, C19.2, C20.2, C21.2, C22.2, C25.2, C27.2, C28.2, C30.2, C31.2, C32.2, C33.2, C34.2, C35.2, C36.2, C37.2, C38.2, C39.2, C40.2, C41.2, C42.2, C43.2, C44.2, C45.2, C46.2, C47.2, C48.2, C49.2, D1.2 (GND), D2.2 (GND), D3.2 (GND), D4.2 (VN), D5.3 (common), D6.3 (A), D7.3 (GND), D7.8 (GND), D8.2 (A2), D10.1 (K), D11.1 (K), D15.2 (A2), D16.2 (A2), D19.2 (VN), D20.2 (GND), F3.2, J2.1 (GND), J2.2 (GND), J2.7 (GND), J2.8 (GND), J2.13 (GND), J2.14 (GND), J2.22 (GND), J2.23 (GND), J2.32 (GND), J2.33 (GND), J2.42 (GND), J2.43 (GND), J2.52 (GND), J2.53 (GND), J2.59 (GND), J2.60 (GND), J2.65 (GND), J2.66 (GND), J2.71 (GND), J2.74 (GND), J2.98 (GND)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
HDMI1_CEC: D19.1 (IO1), J2.149 (HDMI1_CEC), J16.13 (CEC)
HDMI1_CK_N: J2.166 (HDMI1_CLK_N), J16.12 (CK-)
HDMI1_CK_P: J2.164 (HDMI1_CLK_P), J16.10 (CK+)
HDMI1_D0_N: J2.160 (HDMI1_TX0_N), J16.9 (D0-)
HDMI1_D0_P: J2.158 (HDMI1_TX0_P), J16.7 (D0+)
HDMI1_D1_N: J2.154 (HDMI1_TX1_N), J16.6 (D1-)
HDMI1_D1_P: J2.152 (HDMI1_TX1_P), J16.4 (D1+)
HDMI1_D2_N: J2.148 (HDMI1_TX2_N), J16.3 (D2-)
HDMI1_D2_P: J2.146 (HDMI1_TX2_P), J16.1 (D2+)
HDMI1_HPD: D19.6 (IO4), J2.143 (HDMI1_HOTPLUG), J16.19 (HPD)
HDMI1_SCL: D19.3 (IO2), J2.147 (HDMI1_SCL), J16.15 (SCL)
HDMI1_SDA: D19.4 (IO3), J2.145 (HDMI1_SDA), J16.16 (SDA)
HDMI_5V: C44.1, J16.18 (+5V), U18.6 (OUT)
HDMI_ILIM: R59.1, U18.5 (ILIM)
HUBUP_DM: J2.165 (USB3-1-DM), U19.10 (DMU)
HUBUP_DP: J2.163 (USB3-1-DP), U19.11 (DPU)
HUB_DM: D2.3 (I/O2), D2.4 (I/O2), J1.34, U19.7 (DM1)
HUB_DP: D2.1 (I/O1), D2.6 (I/O1), J1.35, U19.8 (DP1)
HUB_XI: U19.16 (XI), Y2.1
HUB_XO: U19.15 (XO), Y2.3
I2C1_SCL: J2.56 (GPIO3), U4.5 (SCL), U5.5 (SCL)
I2C1_SDA: J2.58 (GPIO2), U4.4 (SDA), U5.4 (SDA)
J1_GND: F3.1, J1.18, J1.33
J10_CC1: J10.A5 (CC1), JP6.1 (A), R43.1
J10_CC2: J10.B5 (CC2), JP7.1 (A), R44.1
J10_VBUS: D15.1 (A1), J10.A4 (VBUS), J10.A9 (VBUS), J10.B4 (VBUS), J10.B9 (VBUS), JP5.1 (A)
LED_3V3: D11.2 (A), R39.2
LED_ACT_A: D12.2 (A), R40.2
LED_BR5V: D10.2 (A), R38.2
LED_ETH2_A: D14.2 (A), R42.2
LED_ETH3_A: D13.2 (A), R41.2
LED_NACT: D12.1 (K), J2.21 (LED_nACT)
MESS_VIN24: R20.2, U4.8 (Vbus)
MUX_ILM: R31.1, U8.10 (ILM)
MUX_IN2: C18.1, JP5.2 (B), U8.2 (IN2)
MUX_OUT: R24.1, U5.10 (Vin+), U8.1 (OUT), U8.8 (OUT)
MUX_PR1: R29.2, R30.1, U8.6 (PR1)
MUX_SS: C8.1, U8.11 (SS)
NRPIBOOT: J2.93 (nRPIBOOT), JP_BOOT.1, TP6.1
OTG_DM: D3.1 (I/O1), D3.6 (I/O1), J2.103 (USB_N), J10.A7 (D-), J10.B7 (D-)
OTG_DP: D3.3 (I/O2), D3.4 (I/O2), J2.105 (USB_P), J10.A6 (D+), J10.B6 (D+)
PMIC_EN: J2.99 (PMIC_Enable), TP5.1
PWR5V_FLT_N: J2.30 (GPIO6), R53.2, U15.4 (~FAULT), U16.4 (~FAULT), U18.4 (~FAULT), U20.4 (~FAULT)
PWR_BUT: J2.92 (PWR_Button), TP7.1
PWR_FAIL_N: J2.48 (GPIO27), R50.2, TP12.1, U4.3 (~Alert)
RS485_A: D5.1 (A1), J1.20, J11.1, JP2.2 (B), R17.1, U3.6 (A)
RS485_A_BIAS: JP2.1 (A), R15.2
RS485_B: D5.2 (A2), J1.19, J11.2, JP3.1 (A), JP_485_TERM.2 (B), U3.7 (B)
RS485_B_BIAS: JP3.2 (B), R16.1
RS485_DE: J2.50 (GPIO17), R13.1, U3.2 (~RE), U3.3 (DE)
RS485_TERM: JP_485_TERM.1 (A), R17.2
TOUCH_DM: D20.3 (I/O2), D20.4 (I/O2), J17.2 (D-), U19.5 (DM2)
TOUCH_DP: D20.1 (I/O1), D20.6 (I/O1), J17.3 (D+), U19.6 (DP2)
UART0_RX: J2.51 (GPIO15), R14.2, U3.1 (RO)
UART0_TX: J2.55 (GPIO14), U3.4 (DI)
UART2_RX: J2.34 (GPIO5), U11.4
UART2_RX_PUF: R2.2, R9.1, U11.2
UART2_TX: J2.54 (GPIO4), R11.2, U10.2
UART2_TX_PUF: R1.2, U10.4
UART3_RX: J2.40 (GPIO9), U17.4
UART3_TX: J2.39 (GPIO8), R56.1
UART4_RX: J2.28 (GPIO13), U13.4
UART4_RX_PUF: R4.2, R10.1, U13.2
UART4_TX: J2.31 (GPIO12), R12.2, U12.2
UART4_TX_PUF: R3.2, U12.4
USB_5V: C48.1, C49.1, D20.5 (VBUS), J17.1 (VBUS), U20.6 (OUT)
USB_ILIM: R60.1, U20.5 (ILIM)
VBUS_EN: J2.111 (VBUS_EN), JP_FAN_EN.1 (A), U20.3 (EN)
VIN24: C9.1, C10.1, C11.1, R20.1, R23.2, TP10.1, U4.9 (Vin-), U7.9 (EN), U7.10 (VIN), U7.11 (VIN), U7.12 (VIN)
VIN24_F: D8.1 (A1), F1.2, R23.1, U4.10 (Vin+)
VIN24_ROH: F1.1, J7.2
WANDLER_5V: C13.1, C14.1, C15.1, C16.1, C17.1, C37.1, C40.1, C43.1, C47.1, L1.2, R26.1, R29.1, U8.7 (IN1), U15.1 (IN), U16.1 (IN), U18.1 (IN), U20.1 (IN)
WANDLER_BOOT: C12.2, U7.4 (BOOT)
WANDLER_FB: R26.2, R27.1, R28.2, U7.7 (FB)
WANDLER_FF: C13.2, R28.1
WANDLER_SW: C12.1, L1.1, U7.1 (SW), U7.2 (SW), U7.3 (SW)

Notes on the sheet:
GND, Spiegel 48 kein GND -> NC
GND, Spiegel 45 kein GND -> NC
5-V-Pegel – NIE anschließen
GND, Spiegel 35 kein GND -> NC
GND, Spiegel 30 kein GND -> NC
GND, Spiegel 28 kein GND -> NC
GND, Spiegel 26 kein GND -> NC
GND, Spiegel 24 kein GND -> NC
GND, Spiegel 22 kein GND -> NC
GND, Spiegel 20 kein GND -> NC
GND, Spiegel 15 kein GND -> NC
GND, Spiegel 12 kein GND -> NC
GND, Spiegel 11 kein GND -> NC
GND, Spiegel 10 kein GND -> NC
GND, Spiegel 9 kein GND -> NC
GND, Spiegel 8 kein GND -> NC
GND, Spiegel 7 kein GND -> NC
CM5 – beide Steckverbinder (Pin-Namen aus dem Datenblatt)
J1 – Original-Flachkabel (Pin n = Breakout n; GND nur 18/33, über PTC F3)
Ethernet – eigener 10/100-Übertrager T1 (Bridge-Board hat keinen), Bob-Smith-Abschluss, ESD
USB Kamera (USB3-0, USB2-Lane) und Hub (USB3-1, USB2-Lane) – nur J1 <-> CM5 + ESD
Notfall-USB-C J10 (stehend, OTG/rpiboot), Jumper JP_BOOT = nRPIBOOT
USB-Hub CH334R am Hub-Port des CM5: Port 1 Flachkabel J1, Port 2 USB-A J17 (Touch), 5 V über U20
DSI-Display J12 an MIPI1 (DSI1): 4 Lanes + Takt, I2C ID_SC/ID_SD, eigene 3,3 V (TLV62569, 2 A); Pad n = Kabelleiter n, Buchse Kontakte oben
5-V-Ausgang J13 für Displays: Lastschalter TPS25221 (2,33–2,63 A) an der Wandler-5,2 V, EN GPIO26, FAULT GPIO6
HDMI-Ausgang J16 (HDMI1, Stecker NICHT bestückt): 4 TMDS-Paare, DDC, CEC, HPD, 5 V begrenzt (U18), ESD D19
Lüfter J14 (wie Raspberry Pi 5): Fan_PWM/Fan_Tacho, 5 V über TPS25221 (0,49–0,60 A), Freigabe VBUS_EN
Konsole J15 (Pi-Debugstecker): UART3 GPIO8/9, RX über Ioff-Puffer, TX wählbar UART3/UART0
UART2 (Düse) / UART4 (Main): Ioff-Puffer + 1 kΩ + ESD
RS485 an UART0 + DE (GPIO17), Bias/Abschluss über Lötbrücken (JP_485_TERM ab Werk offen)
CAN: MCP2518FD (SPI1: GPIO18–21, INT GPIO25) + SN65HVD230, Abschluss JP_CAN_TERM (Lötbrücke, ab Werk zu)
24-V-Eingang J7 (XT30, Kante A): tauschbare Sicherung F1, TVS, Shunt 5 mΩ
24 V -> 5,2 V / 5 A (LMR51450)
5-V-Power-Mux TPS2121 (Wandler vor USB-C), Shunt CM5-5V
INA226 an I2C1: 0x40 Eingang (ALERT = Stromausfall), 0x41 CM5-5V
Anzeige-LEDs
Messpunkte (Unterseite)
Befestigung, Passermarken
ERC-Markierungen
K2-CM5-Träger Alpha 2 – 22.11.2026

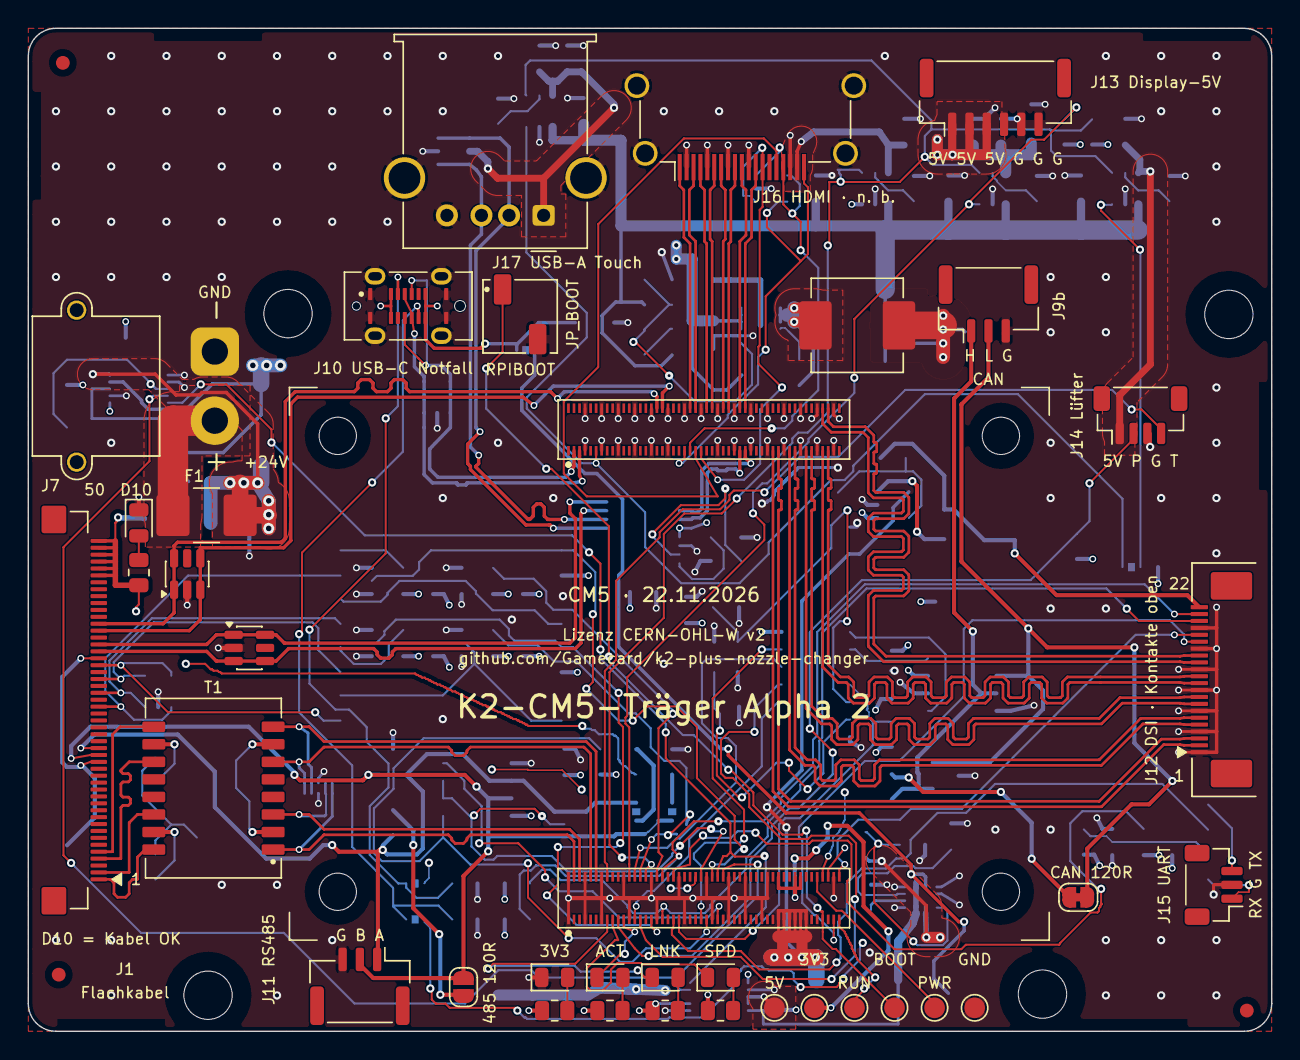
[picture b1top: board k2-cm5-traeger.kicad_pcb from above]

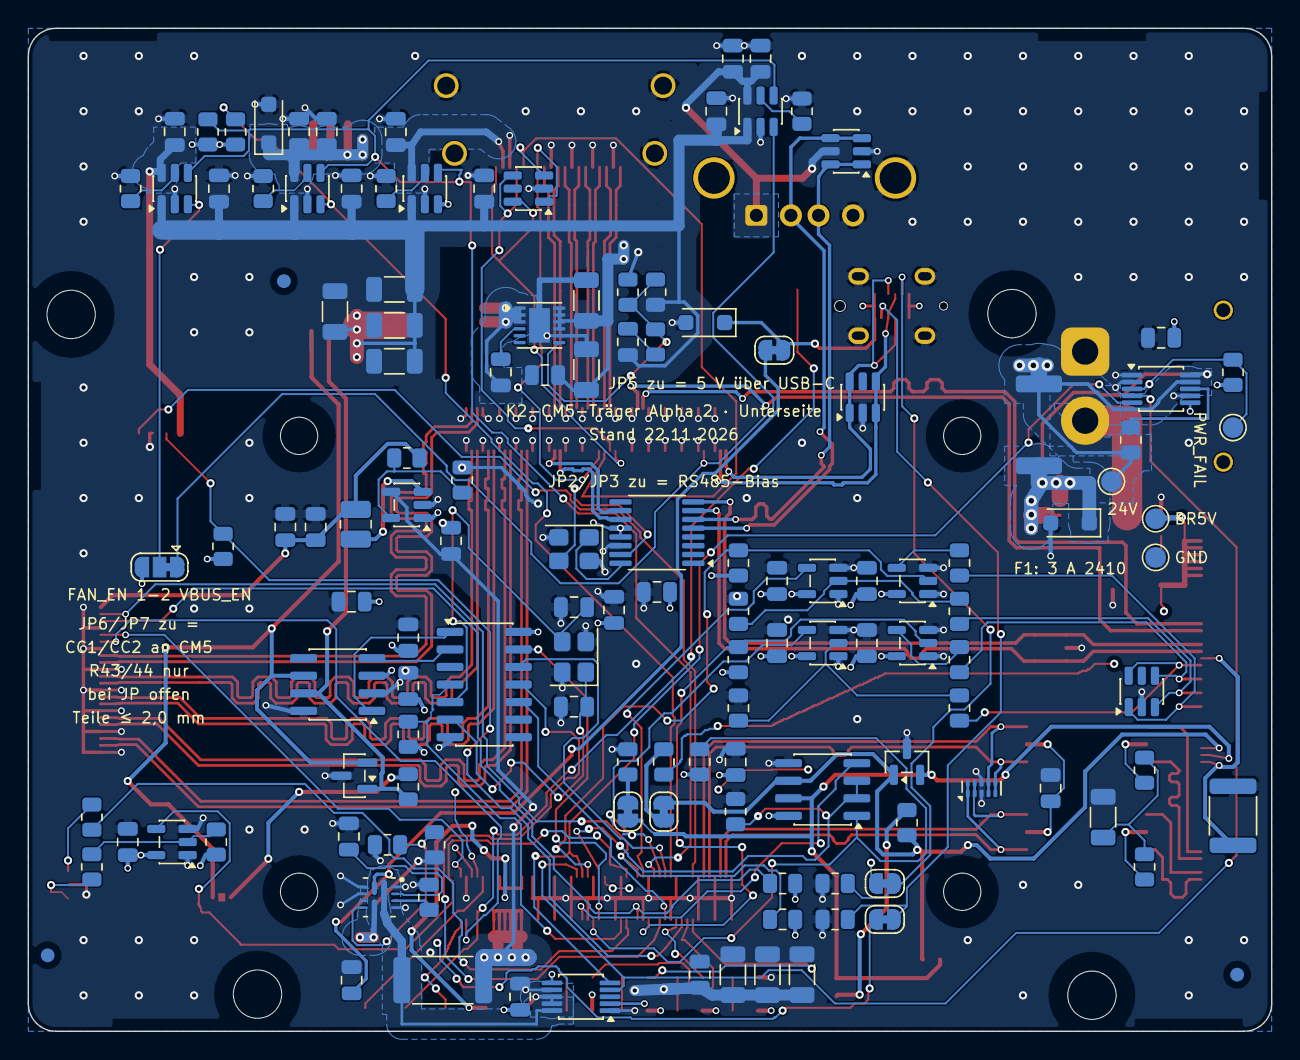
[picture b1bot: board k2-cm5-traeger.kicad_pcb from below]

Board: 4 copper layers, 90.0 x 72.6 mm, 176 parts (133 on the bottom side), 142 nets.

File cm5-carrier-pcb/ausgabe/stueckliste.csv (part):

"Referenzen","Wert","Bemerkung","Bestückung","LCSC","MPN","Hersteller","Footprint","Anzahl","DNP"
"C1,C2","22p","22 pF C0G 0805","Hersteller (JLCPCB SMT)","C1804","CL21C220JBANNNC","Samsung Electro-Mechanics","Capacitor_SMD:C_0805_2012Metric","2",""
"C3,C5-C7,C11,C12,C22,C25,C27,C30-C33,C39,C40,C42,C43,C46,C47","100n","100 nF 50 V X7R 0805","Hersteller (JLCPCB SMT)","C49678","CC0805KRX7R9BB104","YAGEO","Capacitor_SMD:C_0805_2012Metric","19",""
"C4,C18,C34,C37,C41,C44,C45","10u","10 µF 25 V X5R 0805","Hersteller (JLCPCB SMT)","C15850","CL21A106KAYNNNE","Samsung Electro-Mechanics","Capacitor_SMD:C_0805_2012Metric","7",""
"C8","22n","22 nF 50 V X7R 0805","Hersteller (JLCPCB SMT)","C107147","CC0805KRX7R9BB223","YAGEO","Capacitor_SMD:C_0805_2012Metric","1",""
"C9,C10","10u50","10 µF 50 V X5R 1206","Hersteller (JLCPCB SMT)","C13585","CL31A106KBHNNNE","Samsung Electro-Mechanics","Capacitor_SMD:C_1206_3216Metric","2",""
"C13","33p","33 pF C0G 0805","Hersteller (JLCPCB SMT)","C107115","CC0805JRNPO9BN330","YAGEO","Capacitor_SMD:C_0805_2012Metric","1",""
"C14-C17,C19-C21","22u25","22 µF 25 V X5R 1206","Hersteller (JLCPCB SMT)","C12891","CL31A226KAHNNNE","Samsung Electro-Mechanics","Capacitor_SMD:C_1206_3216Metric","7",""
"C28","1n2kV","1 nF 2 kV X7R 1206","Hersteller (JLCPCB SMT)","C9196","1206B102K202NT","FH (Guangdong Fenghua)","Capacitor_SMD:C_1206_3216Metric","1",""
"C35,C36,C38,C48,C49","22u6","22 µF 6,3 V X5R 0805","Hersteller (JLCPCB SMT)","C5674","CL21A226MQQNNNE","Samsung Electro-Mechanics","Capacitor_SMD:C_0805_2012Metric","5",""
"D1,D2","USBLC6-2SC6","ESD USB-Paar, SOT-23-6, OBERSEITE, Durchgang 1–6 / 3–4; VBUS (Pin 5) frei: bei verdrehtem Flachkabel keine Rückspeisung in die CM5-3,3 V","Hersteller (JLCPCB SMT)","C7519","USBLC6-2SC6","STMicroelectronics","Package_TO_SOT_SMD:SOT-23-6","2",""
"D3","USBLC6-2SC6","ESD USB-Paar J10, SOT-23-6, UNTERSEITE; VBUS-Pin offen (wie D1/D2, Pin 5 liegt zwischen den Durchführungen)","Hersteller (JLCPCB SMT)","C7519","USBLC6-2SC6","STMicroelectronics","Package_TO_SOT_SMD:SOT-23-6","1",""
"D4","SRV05-4","ESD 4 Leitungen, SOT-23-6, UNTERSEITE, Flachkabel-Seite; VP (Pin 5) frei","Hersteller (JLCPCB SMT)","C5240367","SRV05-4","TWGMC","Package_TO_SOT_SMD:SOT-23-6","1",""
"D5","SM712","TVS −7/+12 V für RS485, SOT-23, UNTERSEITE","Hersteller (JLCPCB SMT)","C502564","SM712","MDD (Microdiode)","Package_TO_SOT_SMD:SOT-23","1",""
"D6","NUP2105L","ESD CAN, SOT-23, UNTERSEITE","Hersteller (JLCPCB SMT)","C14486","NUP2105LT1G","onsemi","Package_TO_SOT_SMD:SOT-23","1",""
"D7","TPD4E05U06","ESD 4 Kanäle 0,5 pF, USON-10, UNTERSEITE; Durchgangs-Layout (1–10, 2–9, 4–7, 5–6)","Hersteller (JLCPCB SMT)","C138714","TPD4E05U06DQAR","Texas Instruments","Package_SON:USON-10_2.5x1.0mm_P0.5mm","1",""
"D8","SMFJ28A","TVS 28 V uni, SOD-123F, UNTERSEITE; Kathode = Pad 1","Hersteller (JLCPCB SMT)","C5439963","SMFJ28A","BORN","Diode_SMD:D_SOD-123F","1",""
"D10","LED 0805 rot","LED 0805 rot, Kathode = Pad 1","Hersteller (JLCPCB SMT)","C84256","NCD0805R1","Foshan NationStar","LED_SMD:LED_0805_2012Metric","1",""
"D11-D13","LED 0805 grün","LED 0805 grün, Kathode = Pad 1","Hersteller (JLCPCB SMT)","C2297","KT-0805G","Hubei KENTO","LED_SMD:LED_0805_2012Metric","3",""
"D14","LED 0805 gelb","LED 0805 gelb, Kathode = Pad 1","Hersteller (JLCPCB SMT)","C2296","KT-0805Y","Hubei KENTO","LED_SMD:LED_0805_2012Metric","1",""
"D15,D16","SMF5.0A","TVS 5 V unidirektional, SOD-123F, UNTERSEITE; Kathode = Pad 1","Hersteller (JLCPCB SMT)","C193402","SMF5.0A","MDD (Microdiode)","Diode_SMD:D_SOD-123F","2",""
"D19","SRV05-4","ESD für CEC, DDC (SCL/SDA) und Hot-Plug, SOT-23-6, UNTERSEITE; VP frei (keine Rückspeisung)","Hersteller (JLCPCB SMT)","C5240367","SRV05-4","TWGMC","Package_TO_SOT_SMD:SOT-23-6","1",""
"D20","USBLC6-2SC6","ESD USB-A, SOT-23-6, OBERSEITE, Durchgang 1–6 / 3–4, VBUS an USB_5V","Hersteller (JLCPCB SMT)","C7519","USBLC6-2SC6","STMicroelectronics","Package_TO_SOT_SMD:SOT-23-6","1",""
"F1","3A tauschbar","Sicherungshalter Littelfuse 157 (Nano²-Clips) MIT 3-A-Sicherung 453 (sehr flink, 125 V), OBERSEITE (0157003.DR; den Halter gibt es nur mit flinker Sicherung); Sicherung von Hand tauschbar. Ersatz träge: Littelfuse 0452003.MRL (Slo-Blo, LCSC C99550), gleich: 0453003.MR (C178991)","Hersteller (JLCPCB SMT)","C187520","0157003.DR","Littelfuse","k2_traeger:Sicherungshalter_Littelfuse_157_Nano2_2410","1",""
"F3","PTC 0,5A 30V","PTC 0,5 A Halte-/1 A Auslösestrom, 30 V, 1812, UNTERSEITE","Hersteller (JLCPCB SMT)","C12559","SMD1812P050TF/30","PTTC (Polytronics)","Fuse:Fuse_1812_4532Metric","1",""
"H1","Befestigung T113-Platz (M3)","Bohrung Ø 3.5 mm ohne Kupfer (L1); Schraubenkopf ≤ 5.5 mm","– (Bohrung)","","","","k2_traeger:Bohrung_3.5mm_T113_Kopf5.5mm","1",""
"H2","Befestigung T113-Platz (M3)","Bohrung Ø 3.5 mm ohne Kupfer (L2); Schraubenkopf ≤ 5.5 mm","– (Bohrung)","","","","k2_traeger:Bohrung_3.5mm_T113_Kopf5.5mm","1",""
"H3","Befestigung T113-Platz (M3)","Bohrung Ø 3.5 mm ohne Kupfer (L3); Schraubenkopf ≤ 5.5 mm","– (Bohrung)","","","","k2_traeger:Bohrung_3.5mm_T113_Kopf5.5mm","1",""
"H4","Befestigung T113-Platz (M3)","Bohrung Ø 3.5 mm ohne Kupfer (L4); Schraubenkopf ≤ 5.5 mm","– (Bohrung)","","","","k2_traeger:Bohrung_3.5mm_T113_Kopf5.5mm","1",""
"J1","FPC-05FB-50PH20","FFC/FPC-Buchse 50P 0,5 mm, Klappbügel, Kontakte oben+unten, H 2,0 mm (wie V1.5)","Hersteller (JLCPCB SMT)","C2856838","FPC-05FB-50PH20","XUNPU","k2_traeger:FFC_XUNPU_FPC-05FB-50PH20_1x50_P0.5mm_Horizontal","1",""
"J2","CM5 (2x DF40C-100DS-0.4V(51))","2x Hirose DF40C-100DS-0.4V(51) (1,5 mm Stapelhöhe), Lage/Pads nach offiziellen CM-IO-Designdaten; 4x M2,5 (Ø 2,7, ohne Kupfer)","Hersteller (JLCPCB SMT)","C597931","DF40C-100DS-0.4V(51)","Hirose (HRS)","k2_traeger:CM5_Modul_2xDF40C-100DS-0.4V51_1.5mm","1",""
"J7","XT30 24V","XT30PW-M liegend (15 A), Pin 2 = +24 V, Pin 1 = GND (wie „+“/„−“ im Footprint/Datenblatt XT30PW-M); Polarität am Stecker prüfen","Hersteller (JLCPCB SMT) – THT, Handlöten","C431092","XT30PW-M30.G.Y","Changzhou Amass","Connector_AMASS:AMASS_XT30PW-M_1x02_P2.50mm_Horizontal","1",""
"J9b?","CAN H/L/GND","JST GH 3-pol. STEHEND (Top entry, Kabel von oben; 1 = CANH, 2 = CANL, 3 = GND), NUR DATEN – keine 24 V (Toolhead-24 V direkt vom Netzteil, Kabelsicherung ≈ 5 A); ESD über D6 (NUP2105L); gesteckt ≈ 7,3 mm + Kabelbogen","Hersteller (JLCPCB SMT)","C161691","BM03B-GHS-TBT(LF)(SN)","JST","Connector_JST:JST_GH_BM03B-GHS-TBT_1x03-1MP_P1.25mm_Vertical","1",""
"J10","USB-C stehend","USB-C-Buchse 16-pol. STEHEND (Stecker von oben), H 6,8 mm, SMD + Schirmlaschen","Hersteller (JLCPCB SMT)","C5187468","TYPE-C 16P LTH6.8","SHOU HAN","k2_traeger:USB_C_Buchse_stehend_16P_TYPE-C-16P-LTH6.8","1",""
"J11","RS485 A/B/GND","JST GH 3-pol. STEHEND (Top entry, Kabel von oben; 1 = A, 2 = B, 3 = GND), parallel zum THVD1450-Busausgang und FFC 19/20; ESD über D5 (SM712); gesteckt ≈ 7,3 mm + Kabelbogen","Hersteller (JLCPCB SMT)","C161691","BM03B-GHS-TBT(LF)(SN)","JST","Connector_JST:JST_GH_BM03B-GHS-TBT_1x03-1MP_P1.25mm_Vertical","1",""
"J12","DSI 22-pol. Kontakte oben","FPC 22-pol. 0,5 mm, Kontakte OBEN, Schieberverriegelung, H 2,0 mm (GUOCONN 0.5K-AS-22PWB-RW, baugleich HDGC 0.5K-AS-22PWB C2911765); Pad n = Kabelleiter n (Raspberry Pi 5 / CM5-IO-Board): 4 Lanes + Takt, I2C, CAM_GPIO0/1, 3,3 V","Hersteller (JLCPCB SMT)","C53120858","0.5K-AS-22PWB-RW","GUOCONN","k2_traeger:FPC_0.5K-AS-22PWB_1x22_P0.5mm_Kontakte_oben_Horizontal","1",""
"J13","5V Display","JST GH 6-pol. STEHEND (1–3 = 5 V, 4–6 = GND; je Pol drei Kontakte à 1 A), verriegelnd","Hersteller (JLCPCB SMT)","C189892","BM06B-GHS-TBT(LF)(SN)","JST","Connector_JST:JST_GH_BM06B-GHS-TBT_1x06-1MP_P1.25mm_Vertical","1",""
"J14","Lüfter","JST SH 4-pol. STEHEND, Belegung wie Raspberry Pi 5 / CM5-IO-Board J14: 1 = 5 V, 2 = PWM, 3 = GND, 4 = Tacho (Raspberry-Pi-Standard, ohne Rastnase)","Hersteller (JLCPCB SMT)","C495539","BM04B-SRSS-TBT(LF)(SN)","JST","Connector_JST:JST_SH_BM04B-SRSS-TB_1x04-1MP_P1.00mm_Vertical","1",""
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

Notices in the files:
toolhead-pcb/generator/kritisch.py:
SPDX-License-Identifier: GPL-3.0-or-later
cm5-carrier-pcb/k2-cm5-traeger.kicad_pcb:
Lizenz CERN-OHL-W v2 · github.com/Gamecard/k2-plus-nozzle-changer
toolhead-pcb/kopfplatine-p19.kicad_pcb:
Licence: CERN-OHL-W v2
